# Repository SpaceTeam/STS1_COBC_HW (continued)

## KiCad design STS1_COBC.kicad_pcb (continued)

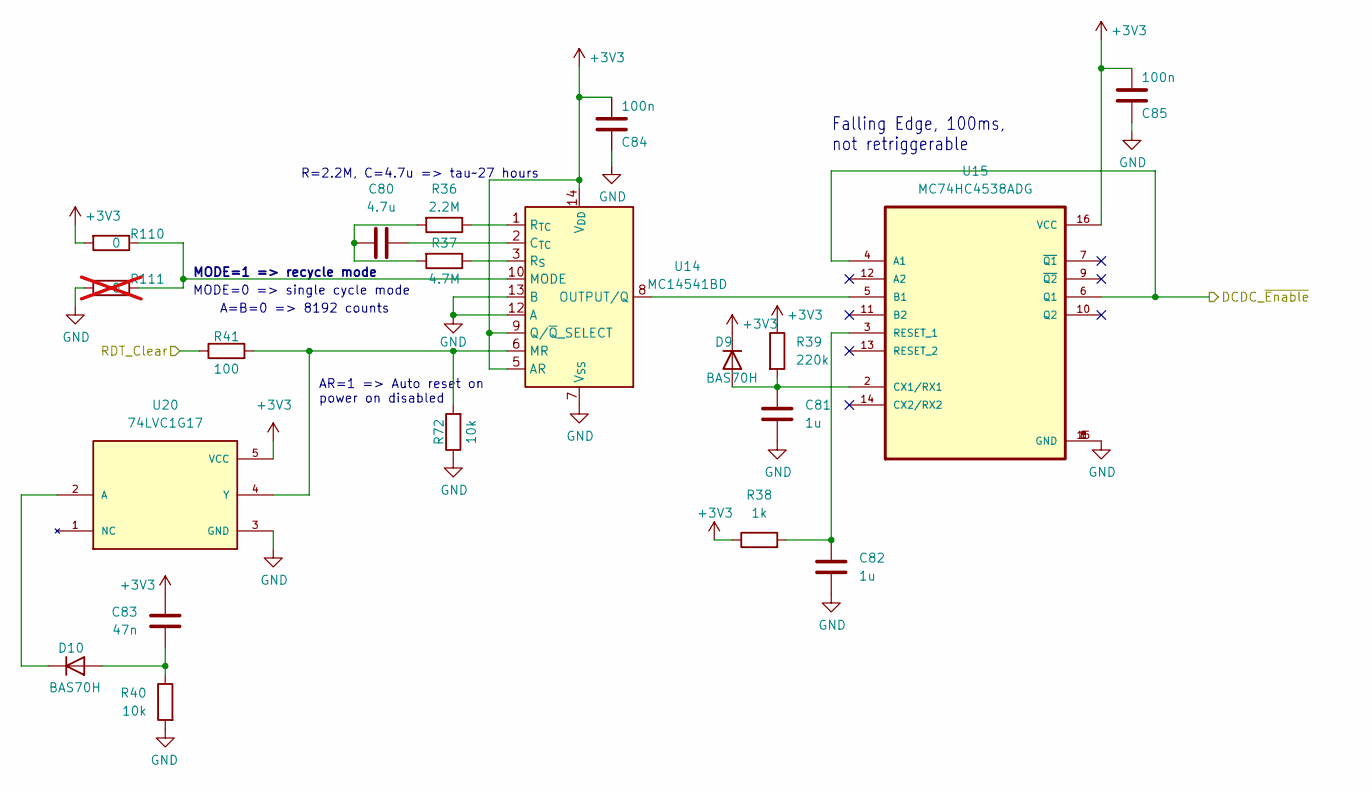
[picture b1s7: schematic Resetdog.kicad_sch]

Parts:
C80: 4.7u; C_0603_1608Metric; Manufacturer_Part_Number CGA3E1X5R0J475KT0Y0E; JLCPCB Part # C338087
C81, C82: 1u; C_0603_1608Metric; Manufacturer_Part_Number CGA3E1X7R1V105KT000N; JLCPCB Part # C342956
C83: 47n; C_0603_1608Metric; Manufacturer_Part_Number C0603C473K5RACAUTO; JLCPCB Part # C129629
C84, C85: 100n; C_0603_1608Metric; Manufacturer_Part_Number C0603C104K5RACAUTO; JLCPCB Part # C129621
D9, D10: BAS70H; D_SOD-123F; Manufacturer_Part_Number BAS70H,115; JLCPCB Part # C426766
R36: 2.2M; R_0603_1608Metric; Manufacturer_Part_Number ESR03EZPF2204; JLCPCB Part # C2103911
R37: 4.7M; R_0603_1608Metric; Manufacturer_Part_Number ESR03EZPF4704; JLCPCB Part # C2103209
R38: 1k; R_0603_1608Metric; Manufacturer_Part_Number ERJ-H3EF1001V; JLCPCB Part # C4073186
R39: 220k; R_0603_1608Metric; Manufacturer_Part_Number ERJ-H3EF5102V; JLCPCB Part # C4285297
R40, R72: 10k; R_0603_1608Metric; Manufacturer_Part_Number ERJ-H3EF1002V; JLCPCB Part # C4297913
R41: 100; R_0603_1608Metric; Manufacturer_Part_Number CRS0603AFX-1000ELF; JLCPCB Part # C2074896
R110: 0; R_0603_1608Metric; Manufacturer_Part_Number ERJ-H3G0R00V; JLCPCB Part # C4117710
R111: 0; R_0603_1608Metric; Manufacturer_Part_Number ERJ-H3G0R00V; JLCPCB Part # C4117710; not fitted
U14: MC14541BD; SOIC-14_3.9x8.7mm_P1.27mm; Manufacturer_Part_Number MC14541BDR2G; JLCPCB Part # C7292
U15: MC74HC4538ADG; SOIC127P600X175-16N; Manufacturer_Part_Number MC74HC4538ADG; JLCPCB Part # C233613
U20: 74LVC1G17; SOT-23-5; Manufacturer_Part_Number SN74LVC1G17DBVRE4; JLCPCB Part # C3753751

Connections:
/DCDC_~Enable: U15.4 (A1), U15.6 (Q1); also elsewhere on the board
/RDT_Clear: R41.1; also elsewhere on the board
unnamed: C80.1, R36.2, R37.2
unnamed: C80.2, U14.2 (C_{TC})
unnamed: R110.1, R111.1, U14.10 (MODE)
unnamed: R41.2, R72.2, U14.6 (MR), U20.4 (Y)
unnamed: U14.8 (OUTPUT/Q), U15.5 (B1)
unnamed: R37.1, U14.3 (R_{S})
unnamed: R36.1, U14.1 (R_{TC})
unnamed: C82.1, R38.2, U15.3 (RESET_1)

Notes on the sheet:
R=2.2M, C=4.7u => tau~27 hours
Falling Edge, 100ms, not retriggerable
MODE=0 => single cycle mode
A=B=0 => 8192 counts
AR=1 => Auto reset on power on disabled
MODE=1 => recycle mode

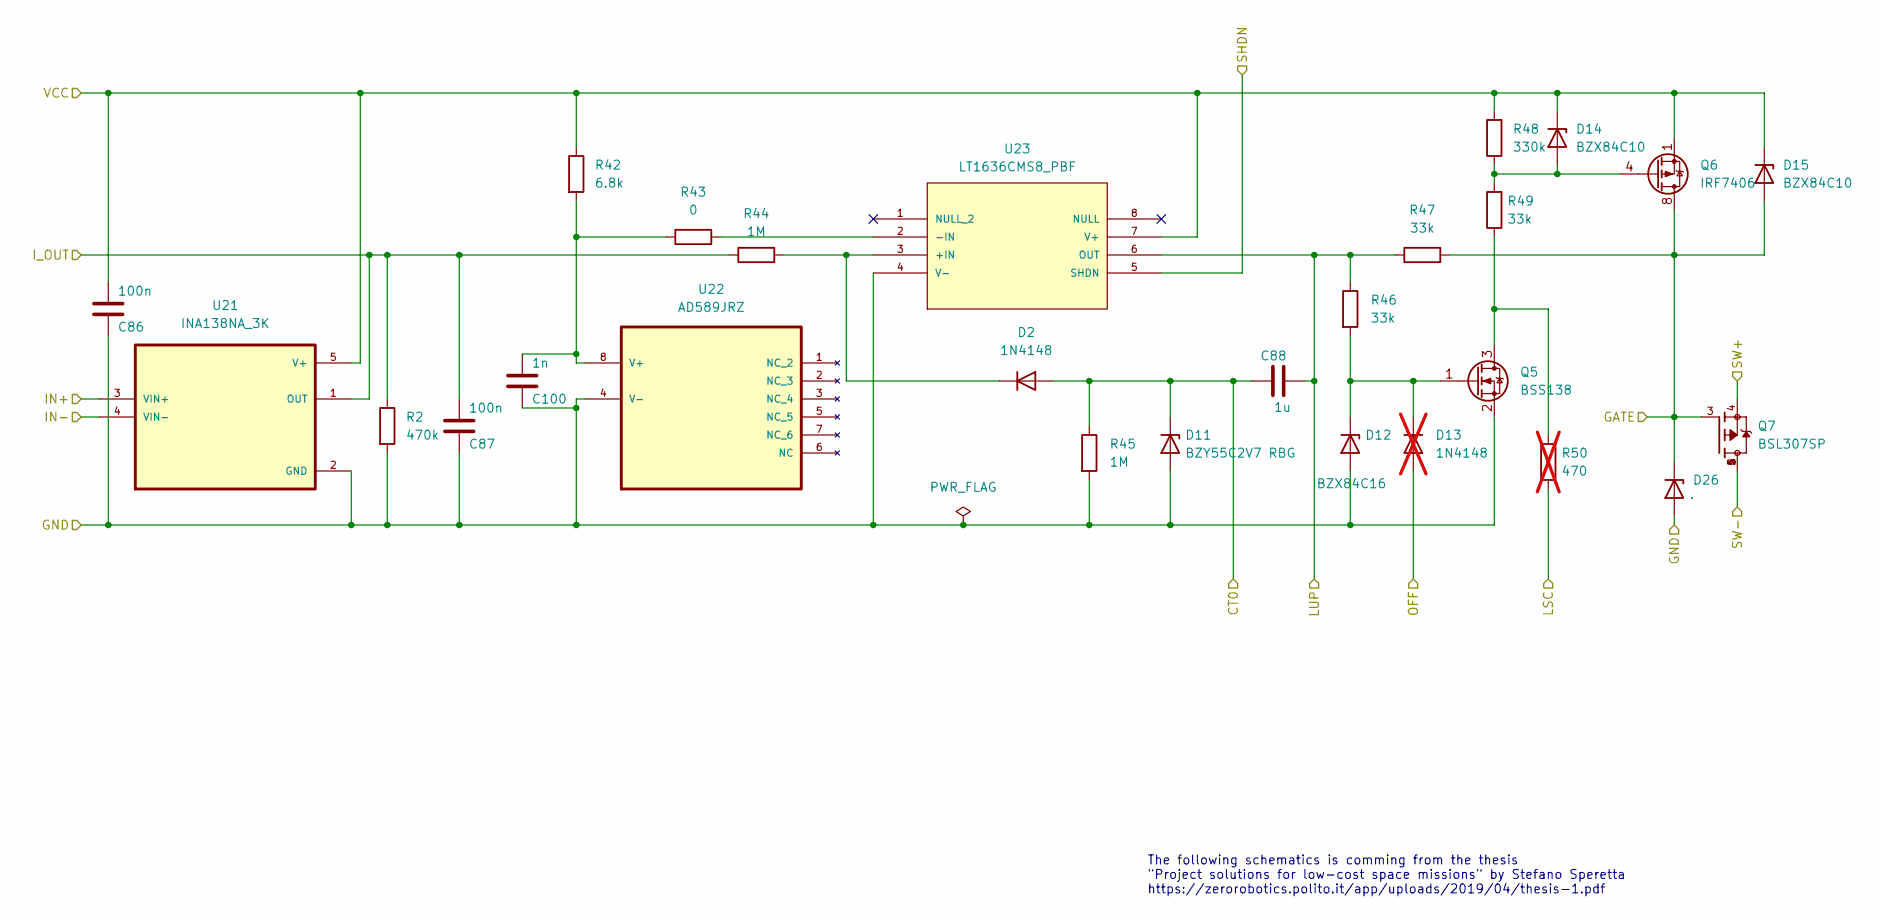
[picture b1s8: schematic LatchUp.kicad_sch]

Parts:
C86, C87: 100n; C_0603_1608Metric; Manufacturer_Part_Number C0603C104K5RACAUTO; JLCPCB Part # C129621
C88: 1u; C_0603_1608Metric; Manufacturer_Part_Number CGA3E1X7R1V105KT000N; JLCPCB Part # C342956
C100: 1n; C_0603_1608Metric; Manufacturer_Part_Number C0603C102K5RACAUTO; JLCPCB Part # C141069
D2: 1N4148; D_SOD-123; Manufacturer_Part_Number 1N4148W-7-F; JLCPCB Part # C83528
D11: BZY55C2V7 RBG; D_0805_2012Metric; Manufacturer_Part_Number BZY55B2V7 RBG
D12: BZX84C16; SOT-23; Manufacturer_Part_Number BZX84-C16,215; JLCPCB Part # C131660
D13: 1N4148; D_SOD-123; Manufacturer_Part_Number 1N4148W-7-F; JLCPCB Part # C83528; not fitted
D14, D15: BZX84C10; SOT-23; Manufacturer_Part_Number BZX84-C10,235; JLCPCB Part # C550933
D26: PTVS5V0S1UR,115; D_SOD-123; Manufacturer_Part_Number PTVS5V0S1UR,115; JLCPCB Part # C478011
Q5: BSS138; SOT-23; Manufacturer_Part_Number BSS138; JLCPCB Part # C52895
Q6: IRF7406; SOIC-8_3.9x4.9mm_P1.27mm; Manufacturer_Part_Number IRF7406TRPBF; JLCPCB Part # C169769
Q7: BSL307SP; TSOP-6_1.65x3.05mm_P0.95mm; Manufacturer_Part_Number BSL307SP H6327; JLCPCB Part # C534457
R2: 470k; R_0603_1608Metric; Manufacturer_Part_Number MR06X4703FTL; JLCPCB Part # C327839
R42: 6.8k; R_0603_1608Metric
R43: 0; R_0603_1608Metric; Manufacturer_Part_Number ERJ-H3G0R00V; JLCPCB Part # C4117710
R44, R45: 1M; R_0603_1608Metric; Manufacturer_Part_Number MR06X1004FTL
R46, R47, R49: 33k; R_0603_1608Metric; Manufacturer_Part_Number ERJ-H3EF3302V; JLCPCB Part # C4220470
R48: 330k; R_0603_1608Metric; Manufacturer_Part_Number MR06X3303FTL
R50: 470; R_0603_1608Metric; not fitted
U21: INA138NA_3K; SOT-23-5; Manufacturer_Part_Number INA138NA/3K; JLCPCB Part # C47914
U22: AD589JRZ; SOIC-8_3.9x4.9mm_P1.27mm; MPN AD589JRZ; JLCPCB Part # C207416
U23: LT1636CMS8_PBF; MSOP-8_3x3mm_P0.65mm; Manufacturer_Part_Number LT1636CMS8#PBF; DIGIKEY_PART_NUMBER LT1636CMS8#PBFND

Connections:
/COBC VR/Latch Up1/GATE: D15.1 (A), D26.1 (K), Q6.5 (D), Q6.6 (D), Q6.7 (D), Q6.8 (D), Q7.3, R47.2; also elsewhere on the board
/COBC VR/Latch Up1/IN-: Q7.4, U21.4 (VIN-); also elsewhere on the board
/COBC VR/Latch Up1/I_OUT: C87.2, R2.1, R44.1, U21.1 (OUT); also elsewhere on the board
/COBC VR/Latch Up1/LUP: C88.1, R46.1, R47.1, U23.6 (OUT); also elsewhere on the board
/COBC VR/Latch Up1/SW-: Q7.1, Q7.2, Q7.5, Q7.6; also elsewhere on the board
/RF_LATCHUP_DIS: U23.5 (SHDN); also elsewhere on the board
unnamed: D2.1 (K), R44.2, U23.3 (+IN)
unnamed: D12.3 (K), Q5.1 (G), R46.2
unnamed: D14.1 (A), Q6.4 (G), R48.1, R49.2
unnamed: Q5.3 (D), R49.1
unnamed: C100.2, R42.2, R43.1, U22.8 (V+)
unnamed: R43.2, U23.2 (-IN)

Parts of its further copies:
C90, C91: 100n; C_0603_1608Metric; Manufacturer_Part_Number C0603C104K5RACAUTO; JLCPCB Part # C129621
C92: 1u; C_0603_1608Metric; Manufacturer_Part_Number CGA3E1X7R1V105KT000N; JLCPCB Part # C342956
C101: 1n; C_0603_1608Metric; Manufacturer_Part_Number C0603C102K5RACAUTO; JLCPCB Part # C141069
D17: 1N4148; D_SOD-123; Manufacturer_Part_Number 1N4148W-7-F; JLCPCB Part # C83528
D18: BZY55C2V7 RBG; D_0805_2012Metric; Manufacturer_Part_Number BZY55B2V7 RBG
D19: BZX84C16; SOT-23; Manufacturer_Part_Number BZX84-C16,215; JLCPCB Part # C131660
D21, D22: BZX84C10; SOT-23; Manufacturer_Part_Number BZX84-C10,235; JLCPCB Part # C550933
D28: PTVS5V0S1UR,115; D_SOD-123; Manufacturer_Part_Number PTVS5V0S1UR,115; JLCPCB Part # C478011
Q9: BSS138; SOT-23; Manufacturer_Part_Number BSS138; JLCPCB Part # C52895
Q10: IRF7406; SOIC-8_3.9x4.9mm_P1.27mm; Manufacturer_Part_Number IRF7406TRPBF; JLCPCB Part # C169769
Q11: BSL307SP; TSOP-6_1.65x3.05mm_P0.95mm; Manufacturer_Part_Number BSL307SP H6327; JLCPCB Part # C534457
R59: 470k; R_0603_1608Metric; Manufacturer_Part_Number MR06X4703FTL; JLCPCB Part # C327839
R60: 6.8k; R_0603_1608Metric
R61: 0; R_0603_1608Metric; Manufacturer_Part_Number ERJ-H3G0R00V; JLCPCB Part # C4117710
R62, R63: 1M; R_0603_1608Metric; Manufacturer_Part_Number MR06X1004FTL
R64, R65, R67: 33k; R_0603_1608Metric; Manufacturer_Part_Number ERJ-H3EF3302V; JLCPCB Part # C4220470
R66: 330k; R_0603_1608Metric; Manufacturer_Part_Number MR06X3303FTL
U25: INA138NA_3K; SOT-23-5; Manufacturer_Part_Number INA138NA/3K; JLCPCB Part # C47914
U26: AD589JRZ; SOIC-8_3.9x4.9mm_P1.27mm; MPN AD589JRZ; JLCPCB Part # C207416
U27: LT1636CMS8_PBF; MSOP-8_3x3mm_P0.65mm; Manufacturer_Part_Number LT1636CMS8#PBF; DIGIKEY_PART_NUMBER LT1636CMS8#PBFND

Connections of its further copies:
/COBC VR/Latch Up/CT0: C92.2, D17.2 (A), D18.1 (K), R63.1
/COBC VR/Latch Up/GATE: D22.1 (A), D28.1 (K), Q10.5 (D), Q10.6 (D), Q10.7 (D), Q10.8 (D), Q11.3, R65.2; also elsewhere on the board
/COBC VR/Latch Up/IN-: Q11.4, U25.4 (VIN-); also elsewhere on the board
/COBC VR/Latch Up/I_OUT: C91.2, R59.1, R62.1, U25.1 (OUT); also elsewhere on the board
/COBC VR/Latch Up/LUP: C92.1, R64.1, R65.1, U27.6 (OUT)
/COBC VR/Latch Up/SW-: Q11.1, Q11.2, Q11.5, Q11.6; also elsewhere on the board
unnamed: D17.1 (K), R62.2, U27.3 (+IN)
unnamed: D19.3 (K), Q9.1 (G), R64.2
unnamed: D21.1 (A), Q10.4 (G), R66.1, R67.2
unnamed: Q9.3 (D), R67.1
unnamed: C101.2, R60.2, R61.1, U26.8 (V+)
unnamed: R61.2, U27.2 (-IN)

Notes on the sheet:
The following schematics is comming from the thesis "Project solutions for low-cost space missions" by Stefano Speretta https://zerorobotics.polito.it/app/uploads/2019/04/thesis-1.pdf

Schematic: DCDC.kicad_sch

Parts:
C36, C37, C39: Voltage 24V
C38, C41, C42, C43, C44: (no value)
C40, C45, C46: Voltage 10V
C47: Voltage 5V
D9, D10, D11: (no value)
L2: Part 7447706047
Q2: (no value)
R14, R15, R16, R17, R18, R19: (no value)
U6: (no value)

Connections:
/DCDC_~Enable: R14.2; also elsewhere on the board
unnamed: C39.1, R16.2
unnamed 123: Q2.3 (D), R17.2, R18.1, U6.3 (EN); also elsewhere on the board
unnamed: C42.2, U6.16 (BST1)
unnamed: C43.2, U6.13 (BST2)
unnamed: C41.1, R19.1, U6.7 (OC)
unnamed: C42.1, L2.1, U6.15 (SW1)
unnamed: C43.1, L2.2, U6.14 (SW2)
unnamed: C40.1, U6.9 (VCC)

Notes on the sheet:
Undervoltage Lockout at 3.99V Startup at 4.4V

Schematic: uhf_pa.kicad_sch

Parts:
C67: 50p; C_0402_1005Metric; PartNumber CC0402JRNPO9BN500; JLCPCB Part # C576707
C68: 100n; C_0402_1005Metric; PartNumber CGA2B3X5R1H104K050BB; JLCPCB Part # C2168987
C70, C75, C76: 100p; C_0402_1005Metric; PartNumber CBR04C101J3GAC; JLCPCB Part # C386123
C71: 10u; C_0805_2012Metric; PartNumber EMK212BB7106KG-T; JLCPCB Part # C2182156
C72: 100n; C_0805_2012Metric; Manufacturer_Part_Number C0805C104K1RACAUTO; JLCPCB Part # C141125
C73: 10u; CP_EIA-6032-28_Kemet-C; PartNumber T495C106K035ATE400; JLCPCB Part # C1959557
C74: 1n; C_0805_2012Metric; Manufacturer_Part_Number C0805C102J5RACAUTO; JLCPCB Part # C129636
C77: 33p; C_0402_1005Metric; Manufacturer_Part_Number CL05C330JB5NNNC; JLCPCB Part # C70465
C78: 3.3p; C_0402_1005Metric; PartNumber GJM1555C1H3R3WB01D; JLCPCB Part # C88892
FB1: Ferrite_Bead; L_0603_1608Metric; PartNumber BLM18KG331SN1D; JLCPCB Part # C85832
L14: 4n; L_0402_1005Metric; PartNumber LQW15AN6N0B80D; JLCPCB Part # C2043867
L16: 68n; L_0402_1005Metric; PartNumber LQW15AN68NJ0ZD; JLCPCB Part # C2049784
L17: 18n; L_0805_2012Metric; PartNumber LQW2BAN18NG00L; JLCPCB Part # C2042168
L18: 5.6n; L_0402_1005Metric; PartNumber LQW15AN5N6C1ZD
L19: 47n; L_0402_1005Metric; PartNumber LQW15AN47NJ8ZD; JLCPCB Part # C3222081
R27: 240; R_0603_1608Metric; Manufacturer_Part_Number 0603WAJ0241T5E; JLCPCB Part # C25221
R28: 280; R_0603_1608Metric; Manufacturer_Part_Number RC0603FR-07280RL; JLCPCB Part # C482820
R30, R58: 110k; R_0603_1608Metric; Manufacturer_Part_Number ERJ-H3EF1103V; JLCPCB Part # C4176290
R31: 470; R_0603_1608Metric; Manufacturer_Part_Number ERJ-3EKF4700V; JLCPCB Part # C169259
R112: 100; R_0603_1608Metric; Manufacturer_Part_Number CRS0603AFX-1000ELF; JLCPCB Part # C2074896
TP7: GND; TestPoint_Keystone_5015_Micro_Mini; PartNumber 5015
U12: TPS22950_Q1; TSOT-23-6; PartNumber TPS22950CQDDCRQ1; JLCPCB Part # C17349276
U13: TQP7M9106; QFN-24-1EP_4x4mm_P0.5mm_EP2.7x2.7mm_ThermalVias; PartNumber TQP7M9106; JLCPCB Part # C920265

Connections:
+3.3VP: R58.1; also elsewhere on the board
+5VP: C71.2, U12.2 (VIN); also elsewhere on the board
/COBC_RF/RF_LPF1_Out: C67.2, L14.2; also elsewhere on the board
/COBC_RF/RF_LPF2_In: C78.2; also elsewhere on the board
/COBC_RF/UHF_PA/5V_TX_U: C72.1, C73.1, C74.1, C75.1, FB1.2, R27.1, R28.2, U12.5 (VOUT)
/COBC_RF/UHF_PA/PA_Enable: R30.2, U12.1 (ON); also elsewhere on the board
/COBC_RF/UHF_PA/RF_Amp_In: C67.1, U13.4 (RFIN), U13.5 (RFIN)
/COBC_RF/UHF_PA/RF_Amp_Match1: C77.2, L18.1, L19.1
/COBC_RF/UHF_PA/RF_Amp_Match2: C78.1, L19.2
/COBC_RF/UHF_PA/RF_Amp_Out: C77.1, L17.2, U13.14 (RFOUT/VCC), U13.15 (RFOUT/VCC), U13.16 (RFOUT/VCC)
/RF_PA_Fault: R112.1; also elsewhere on the board
unnamed: C68.1, L16.2, R27.2
unnamed: C76.2, FB1.1, L17.1
unnamed: R58.2, R112.2, U12.6 (FLT)
unnamed: R31.1, U12.4 (ILIM)
unnamed: L16.1, U13.18 (IREF)
unnamed: C70.1, R28.1, U13.1 (VBIAS)

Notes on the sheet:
Current limit: 2.65A ILIM = 1.18 * R^(-1.072)
3.3->ON
5.0->ON (8.9mA)

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
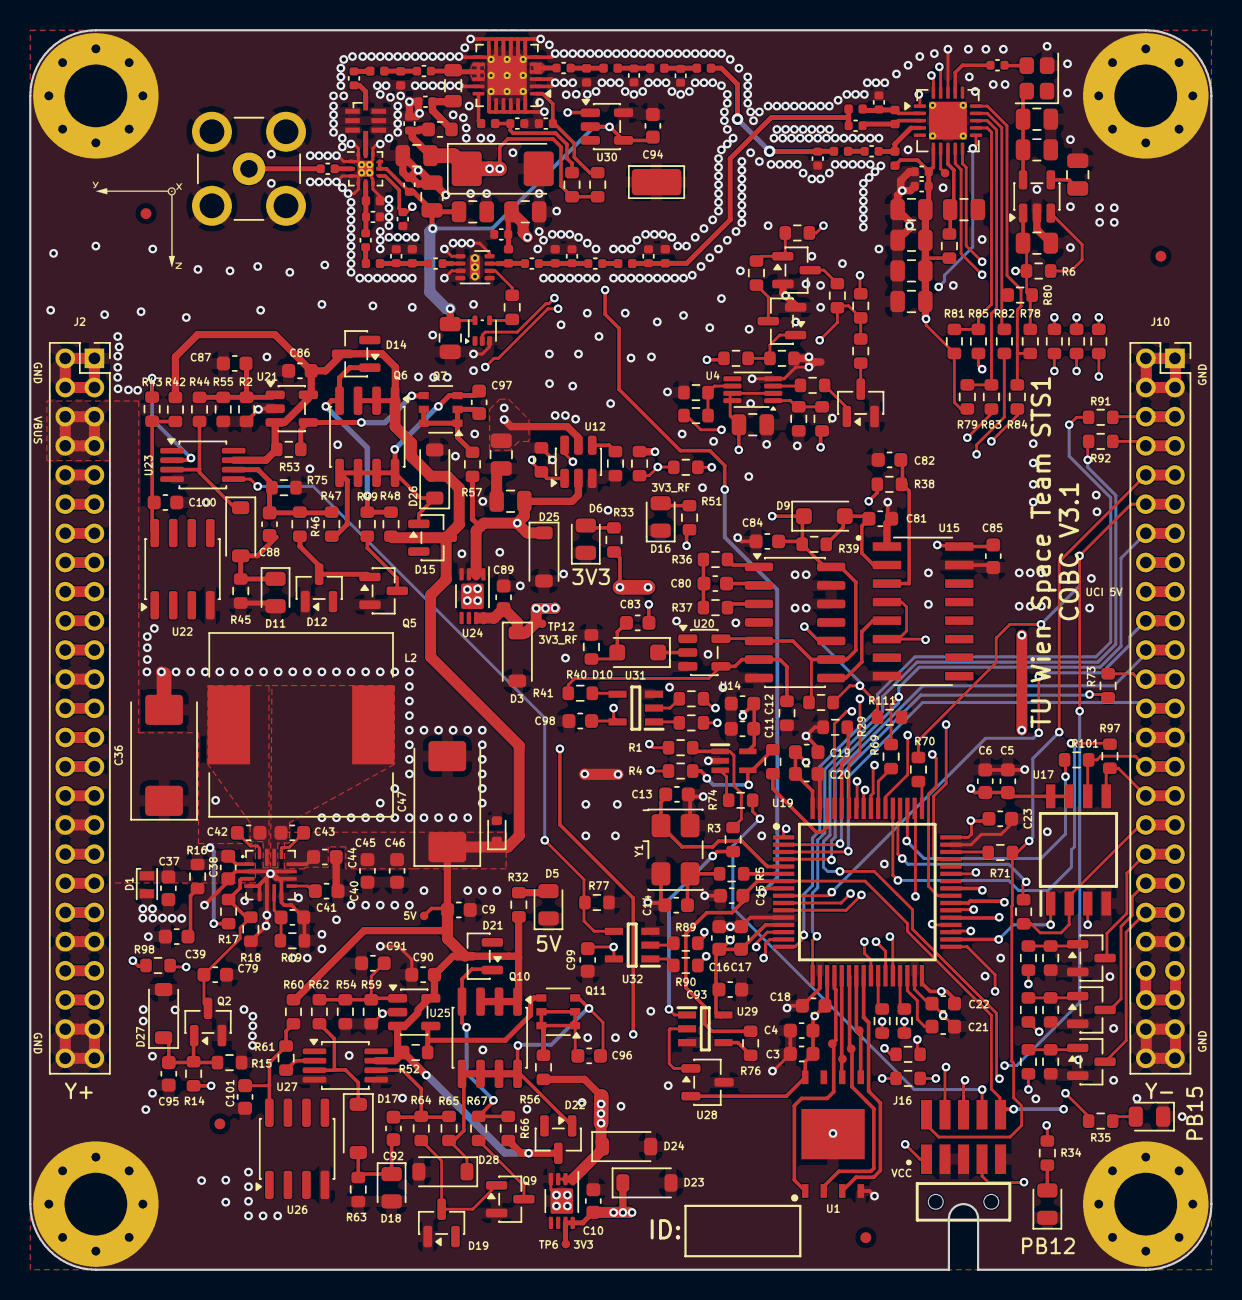
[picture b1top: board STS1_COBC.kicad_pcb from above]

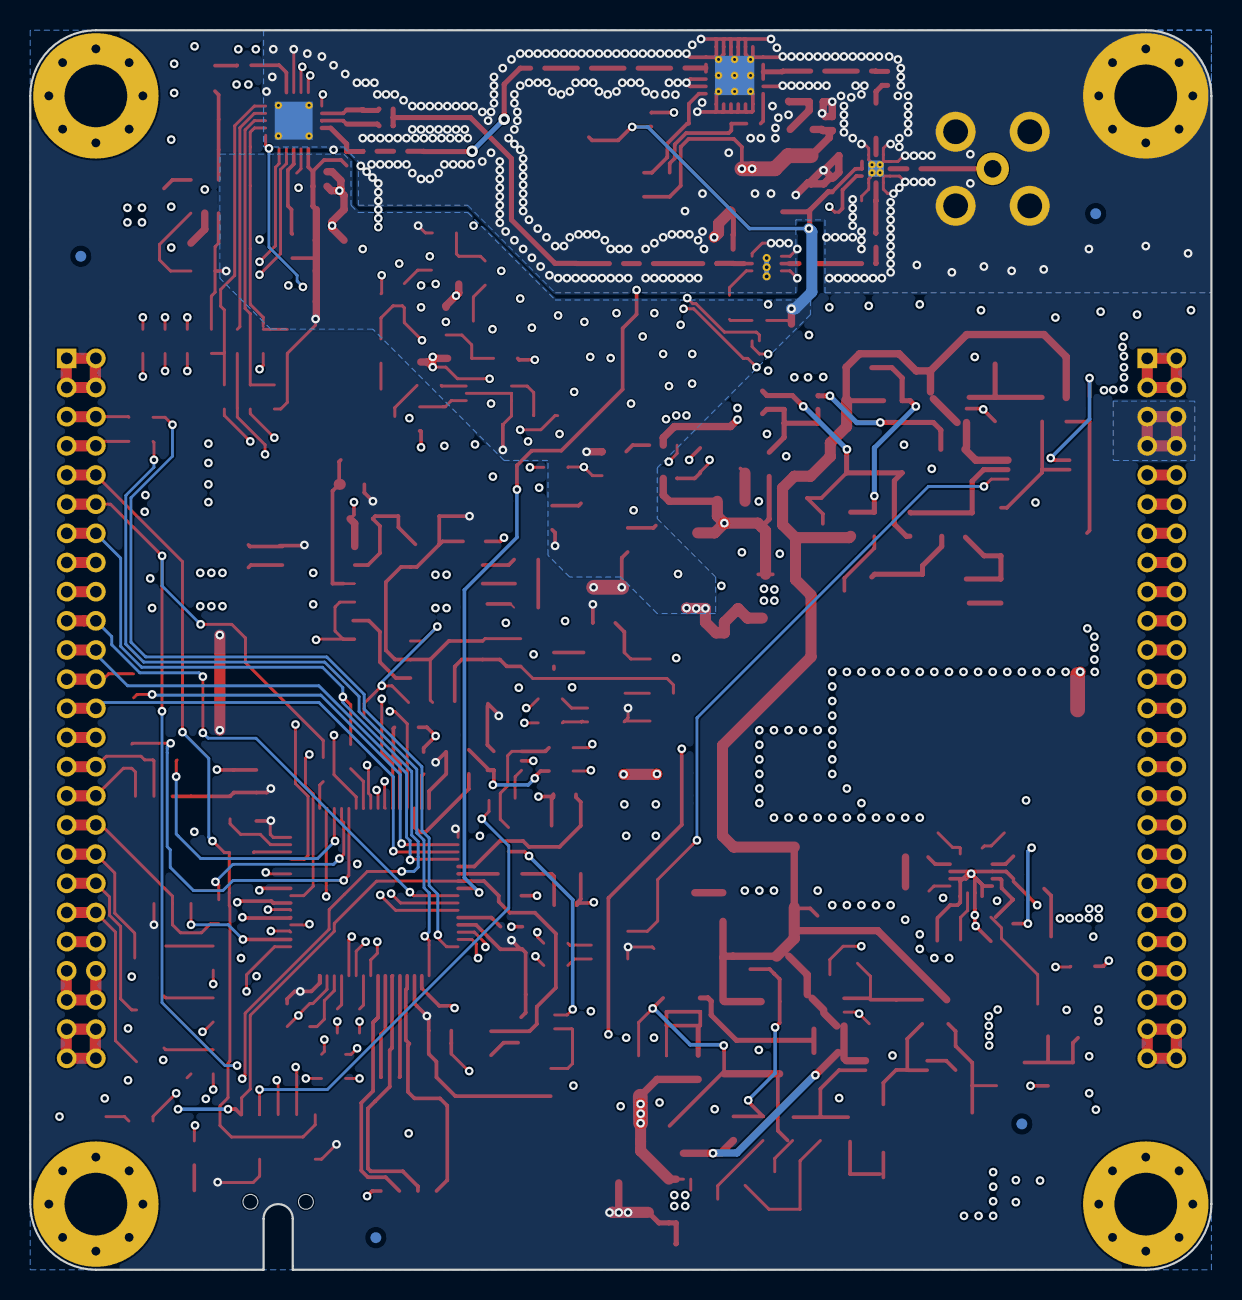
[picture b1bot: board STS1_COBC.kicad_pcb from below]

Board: 4 copper layers, 81.0 x 85.0 mm, 328 parts (4 on the bottom side), 212 nets.

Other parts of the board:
C79: 1u; C_0603_1608Metric
C95: 4.7u; C_0603_1608Metric
D1: UCLAMP0871P.TNT; SGP1610N2
D4: AQ1003-01LTG; D_SOD-523
D27: PTVS5V0S1UR,115; D_SOD-123

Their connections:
unnamed 123: C79.1; also elsewhere on the board

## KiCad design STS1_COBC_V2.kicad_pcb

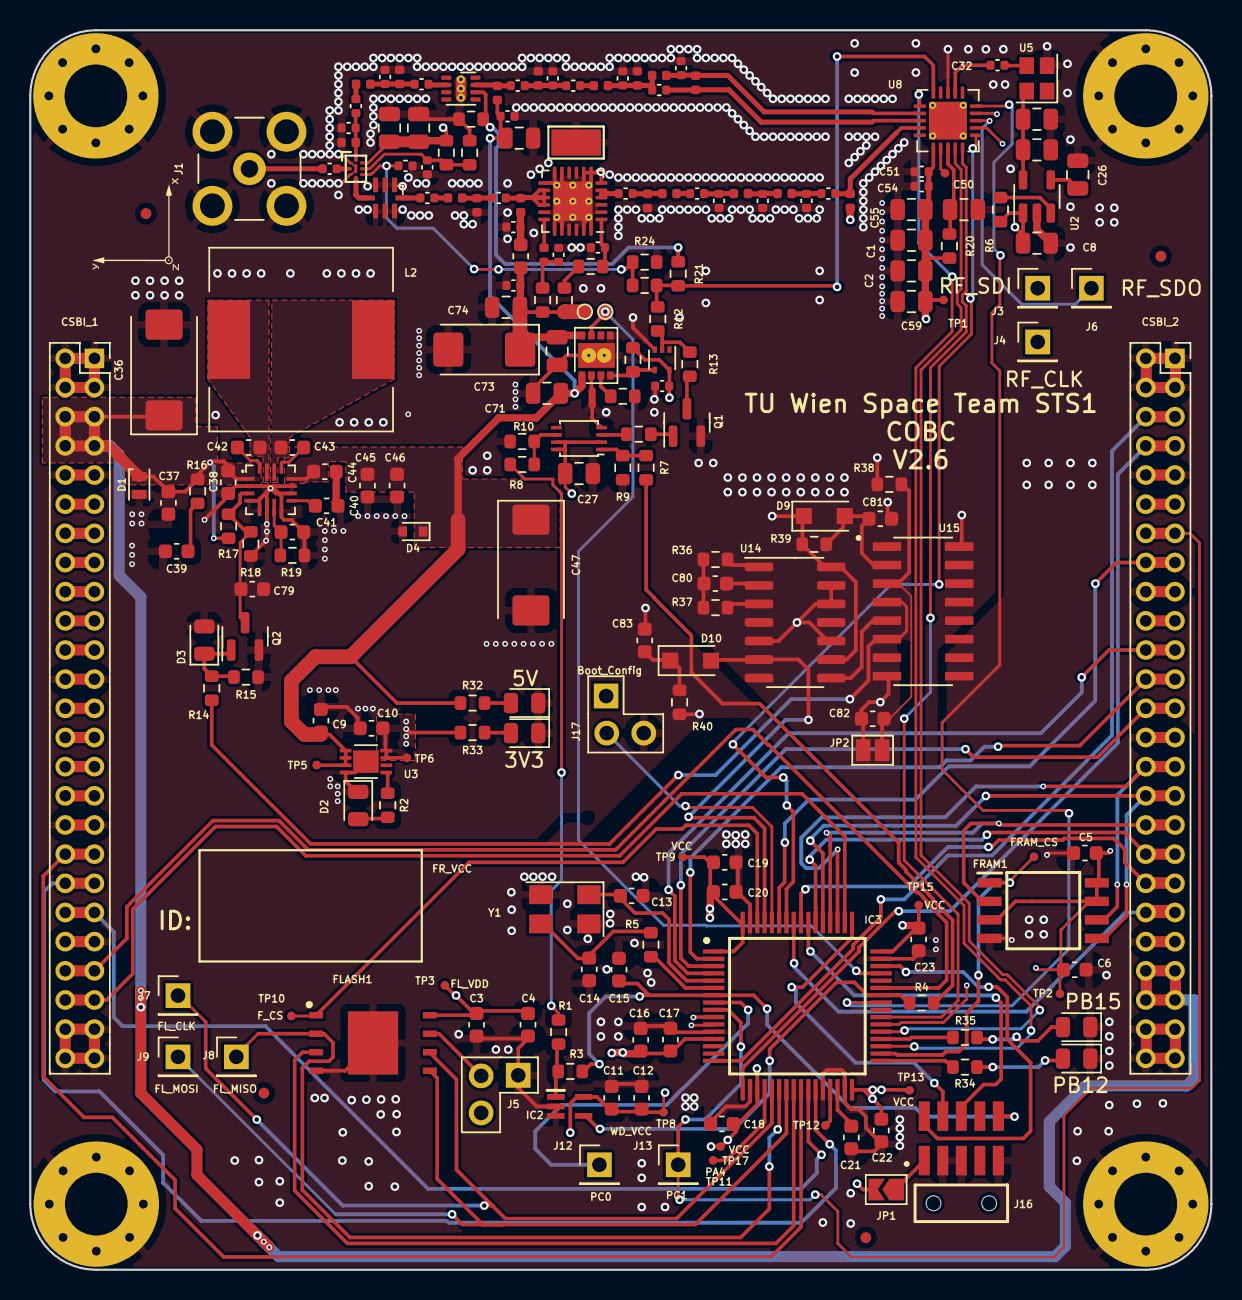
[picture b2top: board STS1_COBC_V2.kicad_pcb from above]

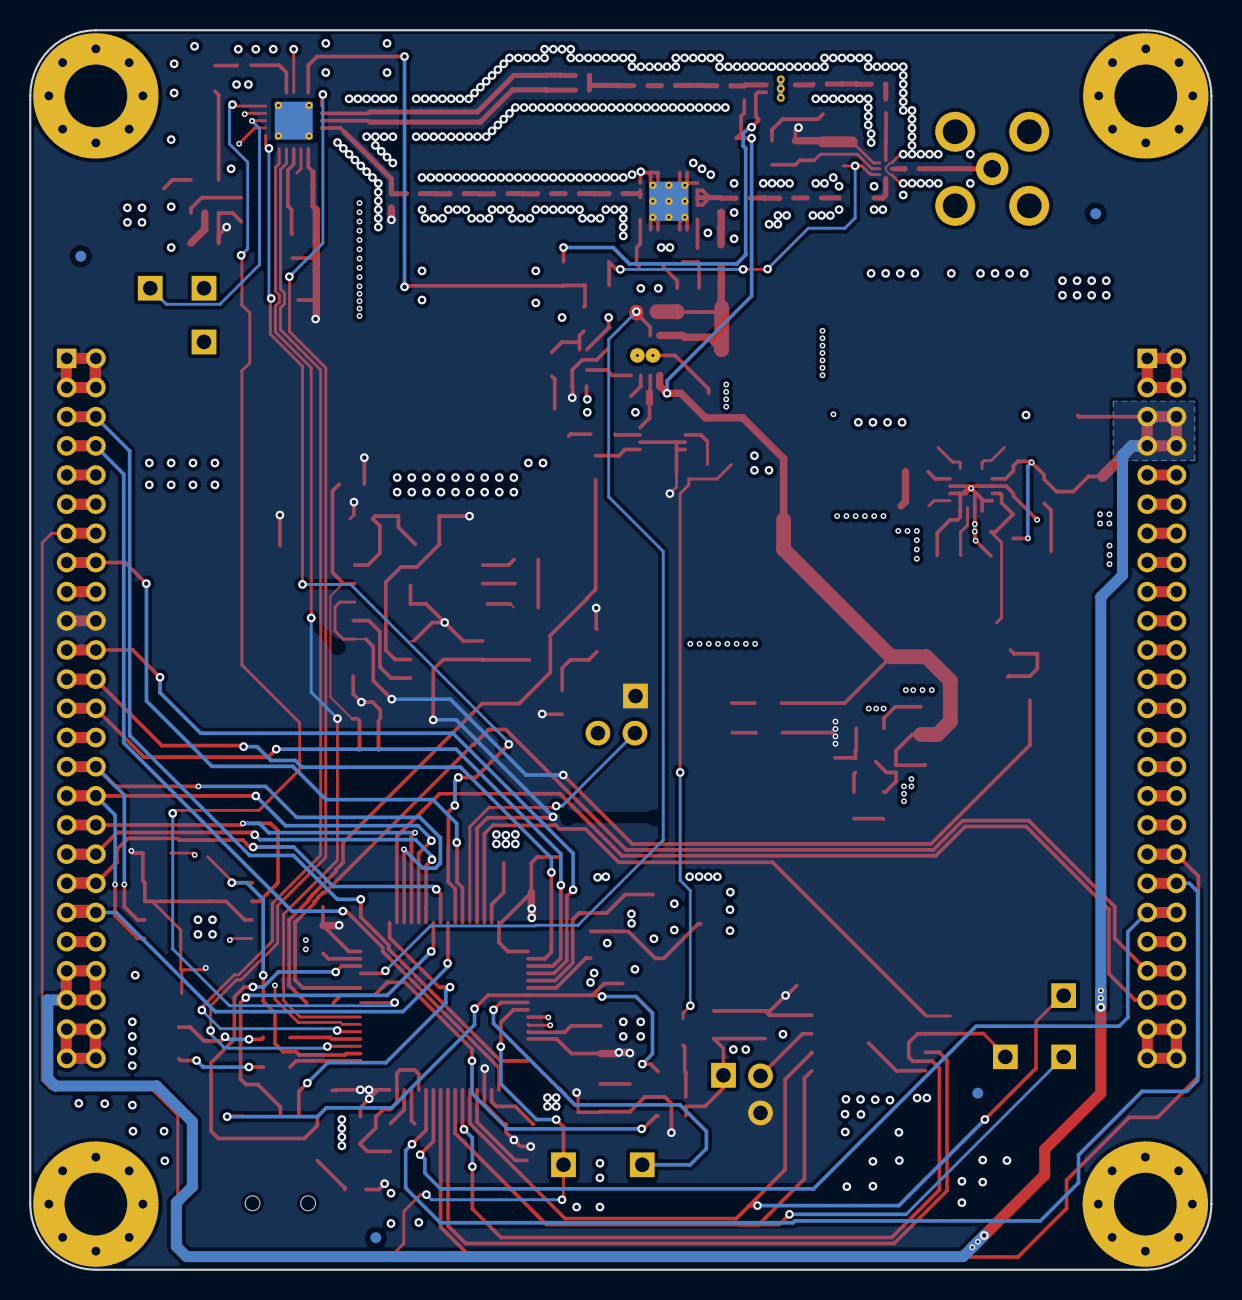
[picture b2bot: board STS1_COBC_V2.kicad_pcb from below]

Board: 4 copper layers, 81.0 x 85.0 mm, 222 parts (4 on the bottom side), 138 nets.

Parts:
C1, C8, C27, C29, C50, C64, C72: 100n; C_0805_2012Metric
C2, C28: 4.7µ; C_0805_2012Metric
C3, C5, C11, C15, C17, C18, C20, C22, C23: 100n; C_0603_1608Metric
C4, C6, C12: 47u; C_0603_1608Metric
C7, C25: 18p; C_0402_1005Metric
C9, C10, C19, C21, C80: 4.7u; C_0603_1608Metric
C13, C14: 20p; C_0603_1608Metric
C16, C81, C82: 1u; C_0603_1608Metric
C24: 12p; C_0402_1005Metric
C26, C55: 10n; C_0805_2012Metric
C30, C34, C56, C61, C77: 24p; C_0402_1005Metric
C31, C32, C35, C49, C53, C54, C62, C63, C66, C70, C75, C76: 100p; C_0402_1005Metric
C33, C60, C67: 2p; C_0402_1005Metric
C36, C47: 100uF; CP_EIA-7343-43_Kemet-X
C37: 22uF; C_0603_1608Metric
C38, C42, C43, C44, C79: 100nF; C_0603_1608Metric
C39, C40: 1uF; C_0603_1608Metric
C41: 22nF; C_0603_1608Metric
C45, C46: 10uF; C_0603_1608Metric
C48: 1u; C_0805_2012Metric
C51: 33p; C_0402_1005Metric
C52: 8.2p; C_0402_1005Metric
C57: 3.9p; C_0402_1005Metric
C58: 2.2p; C_0402_1005Metric
C59: 47µ; C_0805_2012Metric
C65: 1µ; C_0805_2012Metric
C68: 100n; C_0402_1005Metric
C69: 62p; C_0402_1005Metric
C71: 10u; C_0805_2012Metric
C73: 10u; CP_EIA-6032-28_Kemet-C
C74: 1n; C_0805_2012Metric
C78: 3.3p; C_0402_1005Metric
C83: 1n; C_0603_1608Metric
CSBI_1, CSBI_2: PinSocket_2x25_P2.00mm_Vertical
D1: UCLAMP0871P.TNT; SGP1610N2
D2, D5, D6, D7, D8: LED; LED_0805_2012Metric
D3: BZY55C12 RYG; D_0805_2012Metric
D4: AQ1003-01LTG; D_SOD-523
D9, D10: BAS70H; D_SOD-123F
FB1: Ferrite_Bead; L_0603_1608Metric
FID1, FID2, FID3, FID4, FID5, FID6, FID7, FID8: Fiducial; Fiducial_0.75mm_Mask1.5mm
FLASH1: W25Q01JVZEIQ; SON127P800X600X80-9N-D
FRAM1: CY15B108QN-40SXI; SOIC127P800X203-8N
H1, H2, H3, H4: MountingHole_Pad; MountingHole_4.3mm_M4_Pad_Via
IC2: STWD100PYW83F; SOT65P210X110-5N
IC3: STM32F411RET6TR; QFP50P1200X1200X160-64N
J1: UHF; SMB_Jack_Vertical
J3, J4, J6, J7, J8, J9, J12, J13: Conn_01x01_Male; PinHeader_1x01_P2.54mm_Vertical
J5, J17: Conn_01x03_Male; PinHeader_1x03_P2.54mm_Vertical_umdieEcke
J16: Conn_ARM_JTAG_SWD_10; SAMTEC_FTSH-105-01-X-DH-A
JP1: SolderJumper_2_Open; SolderJumper-2_P1.3mm_Open_TrianglePad1.0x1.5mm
JP2: ~{RDT}; SolderJumper-2_P1.3mm_Open_Pad1.0x1.5mm
L1, L3: 15n; L_0402_1005Metric
L2: 4.7uH; L_12x12mm_H6mm
L4, L6, L10, L13: 5.6n; L_0402_1005Metric
L5, L7, L11, L14, L16: 68n; L_0402_1005Metric
L8: 220n; L_0402_1005Metric
L9: 56n; L_0402_1005Metric
L12: 51n; L_0402_1005Metric
L15: 3.2n; L_0402_1005Metric
L17: 18n; L_0402_1005Metric
L18: 8.2n; L_0402_1005Metric
L19: 47n; L_0402_1005Metric
NT1: Net-Tie_2; NetTie-2_SMD_Pad0.5mm
Q1: SQ2318; SOT-23
Q2: BSS123; SOT-23
R1, R3, R4: 4k7; R_0603_1608Metric
R2, R38: 1k; R_0603_1608Metric
R5: 220; R_0603_1608Metric
R6, R17, R30: 100k; R_0603_1608Metric
R7, R8, R11, R13: 100; R_0603_1608Metric
R9, R10, R12, R14, R22: 10k; R_0603_1608Metric
R15: 1M; R_0603_1608Metric
R16: 100mR; R_0603_1608Metric
R18, R21: 33k; R_0603_1608Metric
R19: 21k5; R_0603_1608Metric
R20: 4.7; R_0603_1608Metric
R23, R25: 5.6k; R_0603_1608Metric
R24, R26: 6.8k; R_0603_1608Metric
R27: 240; R_0603_1608Metric
R28: 280; R_0603_1608Metric
R29: 0; R_0603_1608Metric
R31: 110k; R_0603_1608Metric
R32, R33, R34, R35: 220R; R_0603_1608Metric
R36: 2.2M; R_0603_1608Metric
R37: 4.7M; R_0603_1608Metric
R39: 220K; R_0603_1608Metric
R40: 10K; R_0603_1608Metric
TP1: SiVCC; STS1_Testpoint
TP2, TP3, TP5, TP6, TP8, TP9, TP10, TP11, TP12, TP13, TP14, TP15, TP17: TestPoint; STS1_Testpoint
TP4: TXRAMP; STS1_Testpoint
TP7: TestPoint; TestPoint_Keystone_5015_Micro-Minature
TP16: PA_FAULT; TestPoint_D0.8mm_Mask-Only
TP21: 5V_PA; TestPoint_D0.8mm_Mask-Only
U1: coordinate_system; Coordinates
U2: LP2985-1.8; SOT-23-5
U3: MCP1725-3302E_MC; MCP1725-3302E&slash_MC
U4: 74LVC2G74; VSSOP-8_2.4x2.1mm_P0.5mm
U5: TYKTBCSANF-26.000000; Crystal_SMD_2520-4Pin_2.5x2.0mm
U6: MP28167GQ; MP28167_QFN16
U7: NL17SV04XV5T2G; SOT-553
U8: Si4463; QFN-20-1EP_4x4mm_P0.5mm_EP2.6x2.6mm_ThermalVias
U9: LFCG-490+; GE0805C-2
U10: TQP3M9036; DFN-8-1EP_2x2mm_P0.5mm_EP0.7x1.6mm_ThermalVias
U11: QPC1022; Qorvo_9Pin_1.1x1.5mm_LGA
U12: FPF2701; MLP-8
U13: TQP7M9106; QFN-24-1EP_4x4mm_P0.5mm_EP2.7x2.7mm_ThermalVias
U14: MC14541BD; SOIC-14_3.9x8.7mm_P1.27mm
U15: MC74HC4538ADG; SOIC127P600X175-16N
Y1: Crystal_GND24; Crystal_SMD_5032-4Pin_5.0x3.2mm

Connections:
+3V3: C1.1, C2.1, C3.2, C4.2, C5.2, C6.2, C8.1, C10.2, C11.1, C12.1, C16.1, C17.2, C18.2, C19.2, C20.2, C22.1, C23.1, C27.1, C31.2, C51.1, C54.1, C55.1, C59.1, C64.1, C65.1, C83.1, CSBI_2.19, CSBI_2.20, D9.1 (K), FLASH1.8 (VCC), FRAM1.3 (~WP), FRAM1.7 (DNU), FRAM1.8 (VDD), IC2.5 (VCC), IC3.1 (VBAT), IC3.13 (VDDA/VREF+), IC3.19 (VDD_1), IC3.32 (VDD_2), IC3.48 (VDD_3), IC3.64 (VDD_4), J5.3, J17.1, JP1.2 (B), L8.2, R6.1, R20.2, R25.1, R30.2, R33.1, R38.1, R39.1, TP1.1, TP2.1, TP3.1, TP6.1, TP8.1, TP9.1, TP13.1, TP15.1, TP17.1, U2.1 (VIN), U3.7 (SENSE), U3.8 (VOUT), U4.2 (D), U4.7 (~PRE), U4.8 (VCC), U7.5 (VCC), U8.6 (VDD), U11.7 (VDD), U14.9 (Q/~Q_SELECT), U14.14 (V_{DD}), U15.16 (VCC)
+5V: C9.2, C44.1, C45.1, C46.1, C47.1, C48.1, C49.1, C71.1, D4.1 (K), L7.2, R32.1, TP5.1, U3.1 (VIN), U3.2 (VIN), U3.3 (*SHDN), U6.12 (OUT), U12.1 (VIN)
/COBC STM/PC0: IC3.8 (PC0), J12.1
/COBC STM/STM32_NRST: C15.2, IC3.7 (NRST), J16.10 (~RESET), R3.2
/COBC STM/SWDCLK: IC3.49 (PA14), J16.4 (SWDCLK/TCK)
/COBC STM/SWDIO: IC3.46 (PA13), J16.2 (SWDIO/TMS)
/COBC STM/SWO: IC3.55 (PB3), J16.6 (SWO/TDO)
/COBC STM/WDT_Clear: IC2.4 (WDI), IC3.42 (PA9), R4.1
/COBC_old_RF/TX_Active: R12.1, R21.2, R23.1, U8.20 (GPIO3)
/COBC_old_RF/UHF_PA/5V_TX_U: C72.1, C73.1, C74.1, C75.1, FB1.2, R27.1, R28.2, TP21.1, U12.8 (VOUT)
/COBC_old_RF/UHF_PA/RF_IN: C25.1, C67.1, L3.2
/COBC_old_RF/UHF_PA/RF_OUT: C78.2, U9.8 (IN)
/COBC_old_RF/UHF_PA/~PA_EN: R30.1, U7.4, U12.4 (ON)
/DCDC_nEN: R14.2, U15.4 (A1), U15.6 (Q1)
/EDU_BOOT: CSBI_2.15, CSBI_2.16, IC3.59 (PB7)
/EDU_EN: CSBI_1.39, CSBI_1.40, IC3.26 (PB0)
/EDU_Heartbeat: CSBI_1.35, CSBI_1.36, IC3.25 (PC5)
/EDU_Update: CSBI_1.37, CSBI_1.38, IC3.27 (PB1)
/EPS_ANT_DEP: CSBI_2.23, CSBI_2.24, IC3.2 (PC13)
/EPS_BAT_FAULT: CSBI_2.13, CSBI_2.14, IC3.9 (PC1), J13.1
/EPS_BAT_GOOD: CSBI_2.21, CSBI_2.22, IC3.4 (PC15-OSC32_OUT)
/EPS_Charging: CSBI_2.25, CSBI_2.26, IC3.3 (PC14-OSC32_IN)
/Flash_WP: FLASH1.3 (~WP_(IO2)), IC3.24 (PC4)
/PA_FAULT: IC3.45 (PA12), TP16.1, U12.7 (FLAGB)
/RDT_CLR: D10.1 (K), IC3.61 (PB8), U14.6 (MR)
/SPI_FLASH_CS: FLASH1.1 (~CS), IC3.62 (PB9), TP10.1
/SPI_FRAM_CS: FRAM1.1 (~CS), IC3.34 (PB13), TP14.1
/SPI_Flash_CLK: FLASH1.6 (CLK), IC3.21 (PA5), J7.1
/SPI_Flash_MISO: FLASH1.2 (DO_(IO1)), IC3.22 (PA6), J8.1
/SPI_Flash_MOSI: FLASH1.5 (DI_(IO0)), IC3.23 (PA7), J9.1
/STS1_connector/COBC_SPI_1: CSBI_2.29, CSBI_2.30, FRAM1.6 (SCK), IC3.51 (PC10)
/STS1_connector/COBC_SPI_2: CSBI_2.31, CSBI_2.32, FRAM1.5 (SI), IC3.53 (PC12)
/STS1_connector/COBC_SPI_3: CSBI_2.33, CSBI_2.34, FRAM1.2 (SO), IC3.52 (PC11)
/STS1_connector/COBC_SPI_4: CSBI_2.35, CSBI_2.36, IC3.54 (PD2)
/STS1_connector/COBC_SPI_5: CSBI_2.37, CSBI_2.38, IC3.56 (PB4)
/STS1_connector/COBC_SPI_6: CSBI_2.39, CSBI_2.40, IC3.57 (PB5)
/STS1_connector/EDU_SPI_1: CSBI_1.21, CSBI_1.22
/STS1_connector/EDU_SPI_2: CSBI_1.19, CSBI_1.20
/STS1_connector/EDU_SPI_3: CSBI_1.17, CSBI_1.18
/STS1_connector/EDU_SPI_4: CSBI_1.15, CSBI_1.16
/STS1_connector/EDU_SPI_5: CSBI_1.13, CSBI_1.14
/STS1_connector/EDU_SPI_6: CSBI_1.11, CSBI_1.12
/STS1_connector/UART_COBC_EDU_1: CSBI_1.45, CSBI_1.46, IC3.50 (PA15)
/STS1_connector/UART_COBC_EDU_2: CSBI_1.43, CSBI_1.44, IC3.43 (PA10)
/STS1_connector/UCI_COBC_UART_1: CSBI_2.5, CSBI_2.6, IC3.16 (PA2)
/STS1_connector/UCI_COBC_UART_2: CSBI_2.7, CSBI_2.8, IC3.17 (PA3)
/Si4463_CLK: IC3.38 (PC7), J4.1, U8.12 (SCLK)
/Si4463_GPIO_0: IC3.37 (PC6), U8.9 (GPIO0)
/Si4463_GPIO_1: IC3.39 (PC8), U8.10 (GPIO1)
/Si4463_SDI: IC3.11 (PC3), J3.1, U8.14 (SDI)
/Si4463_SDN: IC3.35 (PB14), U8.1 (SDN)
/Si4463_SDO: IC3.10 (PC2), J6.1, U8.13 (SDO)
/Si4463_nIRQ: IC3.58 (PB6), U8.11 (~IRQ)
/Si4463_nSEL: IC3.41 (PA8), U8.15 (~SEL)
/WDT_CLR: R4.2, R7.1
/~WDT_TRIG: R1.2, R8.1
AGND: C1.2, C2.2, C3.1, C4.1, C5.1, C6.1, C7.2, C8.2, C9.1, C10.1, C11.2, C12.2, C13.1, C14.1, C15.1, C16.2, C17.1, C18.1, C19.1, C20.1, C21.2, C22.2, C23.2, C24.2, C25.2, C26.2, C27.2, C28.2, C29.2, C30.2, C31.1, C34.2, C36.2, C37.2, C38.2, C39.2, C40.2, C41.2, C44.2, C45.2, C46.2, C47.2, C48.2, C49.2, C50.2, C51.2, C54.2, C55.2, C56.2, C57.2, C59.2, C61.2, C62.2, C63.2, C64.2, C65.2, C68.2, C70.2, C71.2, C72.2, C73.2, C74.2, C75.2, C76.1, C79.2, C81.2, C82.2, CSBI_1.1, CSBI_1.2, CSBI_1.3, CSBI_1.4, CSBI_1.9, CSBI_1.10, CSBI_1.23, CSBI_1.24, CSBI_1.33, CSBI_1.34, CSBI_1.41, CSBI_1.42, CSBI_1.47, CSBI_1.48, CSBI_1.49, CSBI_1.50, CSBI_2.1, CSBI_2.2, CSBI_2.3, CSBI_2.4, CSBI_2.9, CSBI_2.10, CSBI_2.17, CSBI_2.18, CSBI_2.27, CSBI_2.28, CSBI_2.41, CSBI_2.42, CSBI_2.47, CSBI_2.48, CSBI_2.49, CSBI_2.50, D1.2 (A), D2.1 (K), D3.2 (A), D4.2 (A), D5.1 (K), D6.1 (K), D7.1 (K), D8.1 (K), FLASH1.4 (GND), FLASH1.9 (EP), FRAM1.4 (VSS), H1.1, H2.1, H3.1, H4.1, IC2.2 (GND), IC2.3 (~EN), IC3.12 (VSSA/VREF-), IC3.18 (VSS_1), IC3.28 (PB2), IC3.31 (VSS_2), IC3.47 (VSS_3), IC3.63 (VSS_4), J1.2 (Ext), J5.1, J16.3 (GND), J16.5 (GND), J16.9 (GNDDetect), J17.3, JP2.1 (A), L4.1, L6.1, L10.1, L13.1, L15.2, L18.2, NT1.1, Q1.2 (S), Q2.2 (S), R9.2, R10.2, R15.2, R18.2, R19.2, R22.2, R24.2, R26.2, R31.2, R40.2, TP7.1, U2.2 (GND), U3.4 (GND), U3.9 (EP), U4.4 (GND), U5.2 (GND), U6.2 (GND), U6.4 (NC), U6.5 (RSV1), U6.6 (RSV2), U6.8 (NC), U6.10 (AGND), U6.11 (GND), U7.3 (GND), U8.18 (GND), U8.21 (GND), U9.1 (GND), U9.2 (GND), U9.3 (GND), U9.5 (GND), U9.6 (GND), U9.7 (GND), U10.9 (GND), U11.1 (GND), U11.3 (GND), U11.9 (GND), U12.5 (GND), U12.9 (GND), U13.2 (GND), U13.3 (GND), U13.6 (GND), U13.7 (GND), U13.8 (GND), U13.9 (GND), U13.10 (GND), U13.11 (GND), U13.12 (GND), U13.13 (GND), U13.17 (GND), U13.19 (GND), U13.20 (GND), U13.21 (GND), U13.22 (GND), U13.23 (GND), U13.24 (GND), U13.25 (EP), U14.5 (AR), U14.7 (V_{SS}), U14.10 (MODE), U14.12 (A), U14.13 (B), U15.1 (GND), U15.8 (GND), U15.15 (GND), Y1.2, Y1.4
unnamed: C13.2, IC3.5 (PH0-OSC_IN), Y1.1
unnamed: C14.2, R5.2, Y1.3
unnamed: C21.1, IC3.30 (VCAP_1)
unnamed: C24.1, L1.2, L3.1
unnamed: C26.1, U2.4 (BP)
unnamed: C28.1, C29.1, U2.5 (VOUT), U5.4 (VDD)
unnamed: C30.1, C58.2, L4.2, L5.1, L12.2
unnamed: C32.1, U5.3 (OUT)
unnamed: C32.2, U8.17 (XIN)
unnamed: C33.1, L5.2
unnamed: C33.2, C34.1, C35.1, L6.2
unnamed: C35.2, L7.1, U10.7 (RFOUT)
unnamed: C39.1, R16.2
unnamed: C40.1, U6.9 (VCC)
unnamed: C41.1, R19.1, U6.7 (OC)
unnamed: C42.1, L2.1, U6.15 (SW1)
unnamed: C42.2, U6.16 (BST1)
unnamed: C43.1, L2.2, U6.14 (SW2)
unnamed: C43.2, U6.13 (BST2)
unnamed: C50.1, R20.1, U8.8 (VDD)
unnamed: C52.1, L8.1, U8.4 (TX)
unnamed: C7.1, C52.2, L1.1
unnamed: C53.1, U10.2 (RFIN)
unnamed: C53.2, C56.1, L10.2, L11.1
unnamed: C57.1, L9.1, L12.1, U8.2 (RXp)
unnamed: C58.1, L9.2, U8.3 (RXn)
unnamed: C60.1, L11.2
unnamed: C60.2, C61.1, L13.2, U11.8 (RF2)
unnamed: C62.1, R23.2, R24.1, U11.5 (CTRL)
unnamed: C63.1, R25.2, R26.1, U11.6 (EN)
unnamed: C66.1, U11.2 (ANT)
unnamed: C66.2, J1.1 (In)
unnamed: C67.2, L14.1
unnamed: C68.1, L16.2, R27.2
unnamed: C69.1, L14.2, L15.1
unnamed: C69.2, U13.4 (RFIN), U13.5 (RFIN)
unnamed: C70.1, R29.1, U13.1 (VBIAS)
unnamed: C76.2, FB1.1, L17.1
unnamed: C77.1, L17.2, U13.14 (RFOUT/VCC), U13.15 (RFOUT/VCC), U13.16 (RFOUT/VCC)
unnamed: C77.2, L18.1, L19.1
unnamed: C78.1, L19.2
unnamed: C79.1, Q2.3 (D), R17.2, R18.1, U6.3 (EN)
unnamed: C80.1, R36.2, R37.2
unnamed: C80.2, U14.2 (C_{TC})
unnamed: C81.1, D9.2 (A), R39.2, U15.2 (CX1/RX1)
unnamed: C82.1, JP2.2 (B), R38.2, U15.3 (RESET_1)
unnamed: C83.2, D10.2 (A), R40.1
unnamed: D2.2 (A), R2.2
unnamed: D3.1 (K), Q2.1 (G), R14.1, R15.1
unnamed: D5.2 (A), R32.2
unnamed: D6.2 (A), R33.2
unnamed: D7.2 (A), R34.2
unnamed: D8.2 (A), R35.2
unnamed: FLASH1.7 (~HOLD_OR_RESET_(IO3)), J5.2
unnamed: IC2.1 (~WDO), R1.1, R3.1
unnamed: IC3.6 (PH1-OSC_OUT), R5.1
unnamed: IC3.20 (PA4), TP11.1
unnamed: IC3.29 (PB10), TP12.1
unnamed: IC3.33 (PB12), R34.1
unnamed: IC3.36 (PB15), R35.1
unnamed: IC3.60 (BOOT0), J17.2
unnamed: J16.1 (VTref), JP1.1 (A)
unnamed: L16.1, U13.18 (IREF)
unnamed: NT1.2, U12.2 (PGOOD)
unnamed: Q1.1 (G), R11.2
unnamed: Q1.3 (D), R13.1
unnamed: R2.1, U3.5 (PWRGD)
unnamed: R6.2, U2.3 (ON/~OFF)
unnamed: R7.2, R9.1, U4.1 (C)
unnamed: R8.2, R10.1, U4.6 (~CLR)
unnamed: R11.1, U4.3 (~Q)
unnamed: R12.2, R13.2, U7.2
unnamed: R21.1, R22.1, U10.6 (Shut_Down)
unnamed: R28.1, R29.2
unnamed: R31.1, U12.3 (ISET)
unnamed: R36.1, U14.1 (R_{TC})
unnamed: R37.1, U14.3 (R_{S})
unnamed: TP4.1, U8.7 (TXRAMP)
unnamed: U9.4 (OUT), U11.4 (RF1)
unnamed: U14.8 (OUTPUT/Q), U15.5 (B1)
VBUS: C36.1, C37.1, C38.1, CSBI_1.5, CSBI_1.6, CSBI_1.7, CSBI_1.8, CSBI_2.43, CSBI_2.44, CSBI_2.45, CSBI_2.46, D1.1 (K), R16.1, R17.1, U6.1 (IN)
